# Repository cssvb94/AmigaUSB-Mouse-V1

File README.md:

# Amiga USB Mouse V1

USB to Amiga mouse interface using Arduino Pro Mini and USB Host Shield Mini

USB Host Mini and Arduino Pro Mini mounting:

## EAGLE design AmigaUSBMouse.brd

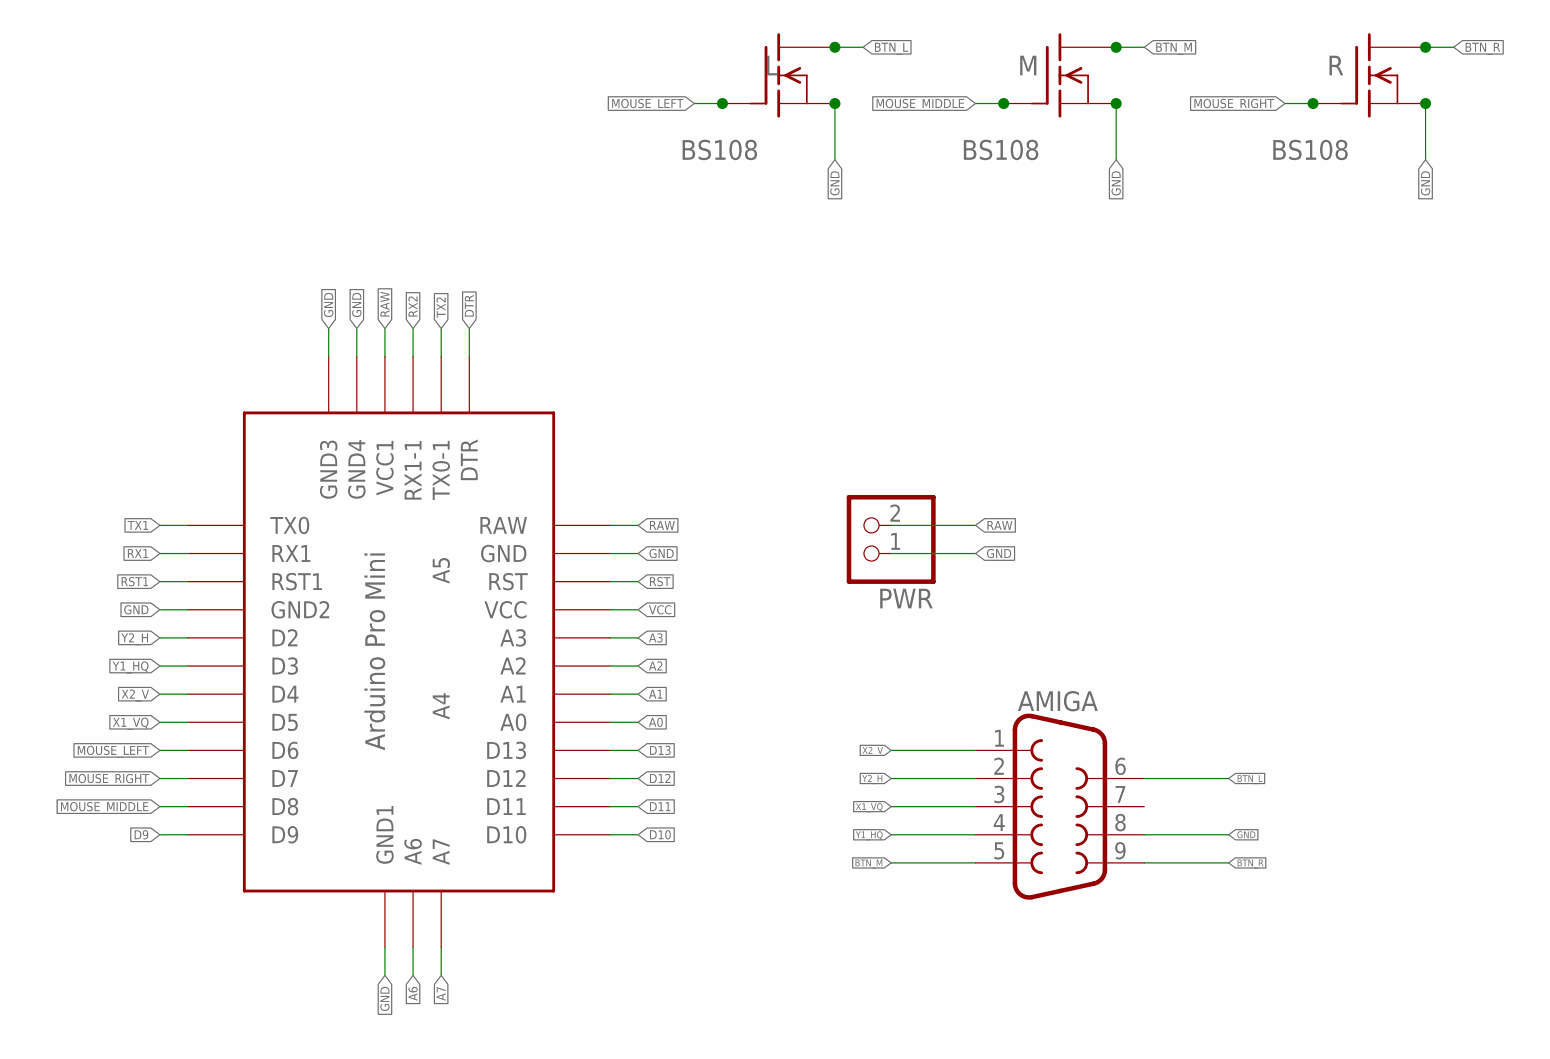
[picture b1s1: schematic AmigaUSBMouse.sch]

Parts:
AMIGA: DB9FEMALE; DB9
L: BS108; TO92-INLINE
M: BS108; TO92-INLINE
PWR: PINHD-1X2; 1X02
R: BS108; TO92-INLINE
U$1: ABK-PRO-MINI

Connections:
A0: U$1.A0
A1: U$1.A1
A2: U$1.A2
A3: U$1.A3
A6: U$1.A6
A7: U$1.A7
BTN_L: AMIGA.6, L.1 (D)
BTN_M: AMIGA.5, M.1 (D)
BTN_R: AMIGA.9, R.1 (D)
D9: U$1.D9
D10: U$1.D10
D11: U$1.D11
D12: U$1.D12
D13: U$1.D13
DTR: U$1.DTR
GND: AMIGA.8, L.3 (S), M.3 (S), PWR.1, R.3 (S), U$1.GND, U$1.GND1 (GND2), U$1.GND2 (GND3), U$1.GND3 (GND4), U$1.GND4 (GND1)
MOUSE_LEFT: L.2 (G), U$1.D6
MOUSE_MIDDLE: M.2 (G), U$1.D8
MOUSE_RIGHT: R.2 (G), U$1.D7
RAW: PWR.2, U$1.RAW, U$1.VCC1
RST: U$1.RST
RST1: U$1.RST1
RX1: U$1.RX1
RX2: U$1.RX1-1
TX1: U$1.TX0
TX2: U$1.TX0-1
VCC: U$1.VCC
X1_VQ: AMIGA.3, U$1.D5
X2_V: AMIGA.1, U$1.D4
Y1_HQ: AMIGA.4, U$1.D3
Y2_H: AMIGA.2, U$1.D2

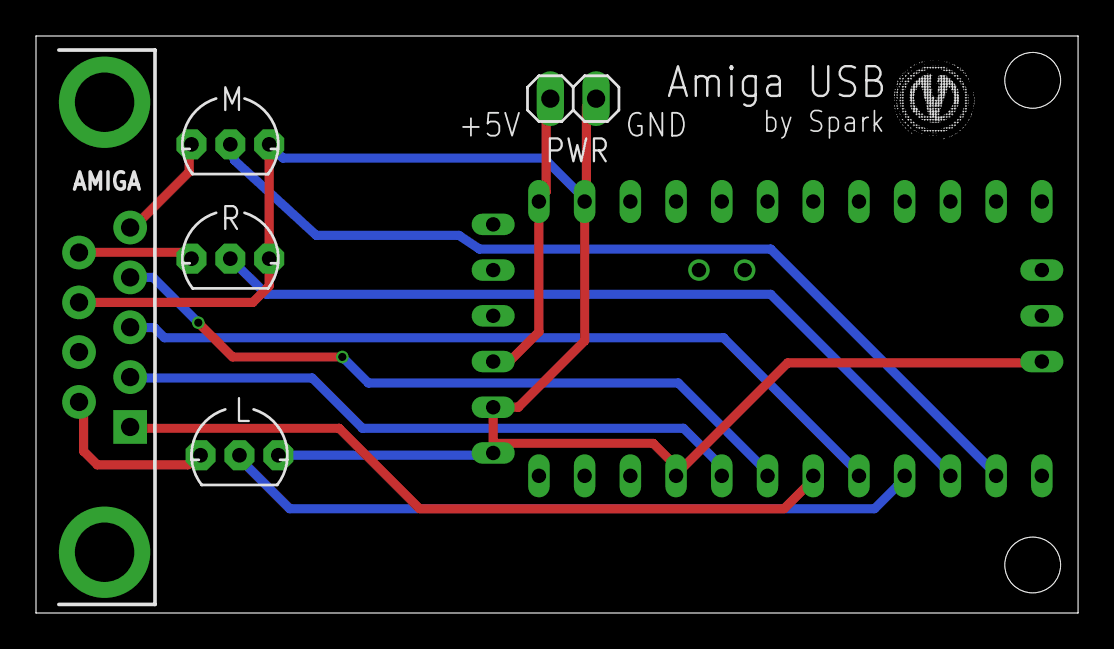
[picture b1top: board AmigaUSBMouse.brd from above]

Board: 2 copper layers, 57.9 x 32.1 mm, 6 parts (0 on the bottom side), 12 nets.

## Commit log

2017-12-08 Initial
2018-01-10 Replaced with MOSFETs
2018-09-18 InitialIgnore
2018-09-18 ReadMe
2018-09-18 PDFs

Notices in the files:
parts and their libraries:
SparkFun-Connectors: Licensing: Creative Commons ShareAlike 4.0 International - https://creativecommons.org/licenses/by-sa/4.0
